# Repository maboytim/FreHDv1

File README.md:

# TRS-HARD disk emulator, aka 'FreHD'

This is a fork of the original FreHD project by Frederic Vecoven.  The original FreHD project can be found on Frederic's site [https://www.vecoven.com/trs80/trs80.html](https://www.vecoven.com/trs80/trs80.html).  The project has since been moved to github at [https://github.com/veco/FreHDv1](https://github.com/veco/FreHDv1) where the latest versions of everything can be found.

The FreHD emulates both the harddisk controller and the disk storage, plus adds many feature which enhance usability.  The FreHD emulates the original TRS-80 harddisk systems such that the original DOS's that supported hardisks should also work with the FreHD using their original harddisk drivers.

The FreHD consists of several components and the scope of the project is really quite amazing.  First there is hardware itself, which uses a PIC microcontroller for a majority of the function, an SD card for the actual storage, a PAL (programmable logic) for miscellaneous logic, and an RTC (realtime clock).  Software (firmware) embedded in the PIC emulates the harddrive and the additional features and provides access to the RTC.  The main purpose of this fork is to provide compatible alternative firmwares, although it goes a bit beyond that.  Although the intent isn't to improve the original project, some improvements and bugfixes have been provided back to the original project.

The equivalent of everything in the original project is included here but might be modified or improved.     My goal is to maintain as much similarity as possible to the original project including the directory structure.  The directory structure is as follows:

+ hw : Hardware files.
  - gal : Equations of the GAL and the compiled jedec file.
  - protel99 : PCB source (schematics and pcb), in Protel99 format for the original PCB design.  Since it is unlikely that anyone is using Protel99 nowadays this is unlikely to change.
  - kicad : PCB source (schematics and pcb), in KiCad format.  This was converted from the original Protel99 design using a conversion script.  It has since been slightly modified and is subject to change.

+ sw : Software files.
  - pic : PIC MPLAB/MPLABX project files, source code, and compiled hex code.
    - trs_hard : 
    - FatFS  : elm FatFS library, ported to PIC18

+ sw/z80
  - fredhd_rom : source code of the boot menu
  - fredhd_rom/rom-patches : patches for all TRS80 models
  - utils : FreHD utilities

To build the PIC software, you will need Microchip C18 compiler (free)
and MPLab (I used version 8.36). You will also need perl, which is
used to compute the CRC16 used by the bootloader. (If you modify the
source, you need to compile twice, the second time to include the
correct CRC in your hex file).

To build the Z80 code, you need zmac. We are using version 1.3, this
assembler is public domain (by Bruce Norskog and others).

To build the rom patches, you need 'asl'. It is available at:
http://john.ccac.rwth-aachen.de:8000/as/

This project started during the long evenings of December 2012, and I
am very proud to release it to the community today, May 12th 2013. 
Many thanks to Andrew Quinn, who beta-tested and motivated me to
finish this project, or at least make it usable :)

One last thing : you may modify, duplicate, enhance or do whatever you
want with the code. All I ask is to keep this README file. You must
make your modifications available (GPL). If you decide to build and
sell (modified) emulators, all I ask is an emulator for my TRS80, so I
can test your changes.

Enjoy !

-Frederic Vecoven (frederic@vecoven.com)

Last update: Thu Jan 23 15:19:26 2014

!!! github !!!
The code is now available on github. I don't have time to
update/polish the code, so contributions are very welcome.

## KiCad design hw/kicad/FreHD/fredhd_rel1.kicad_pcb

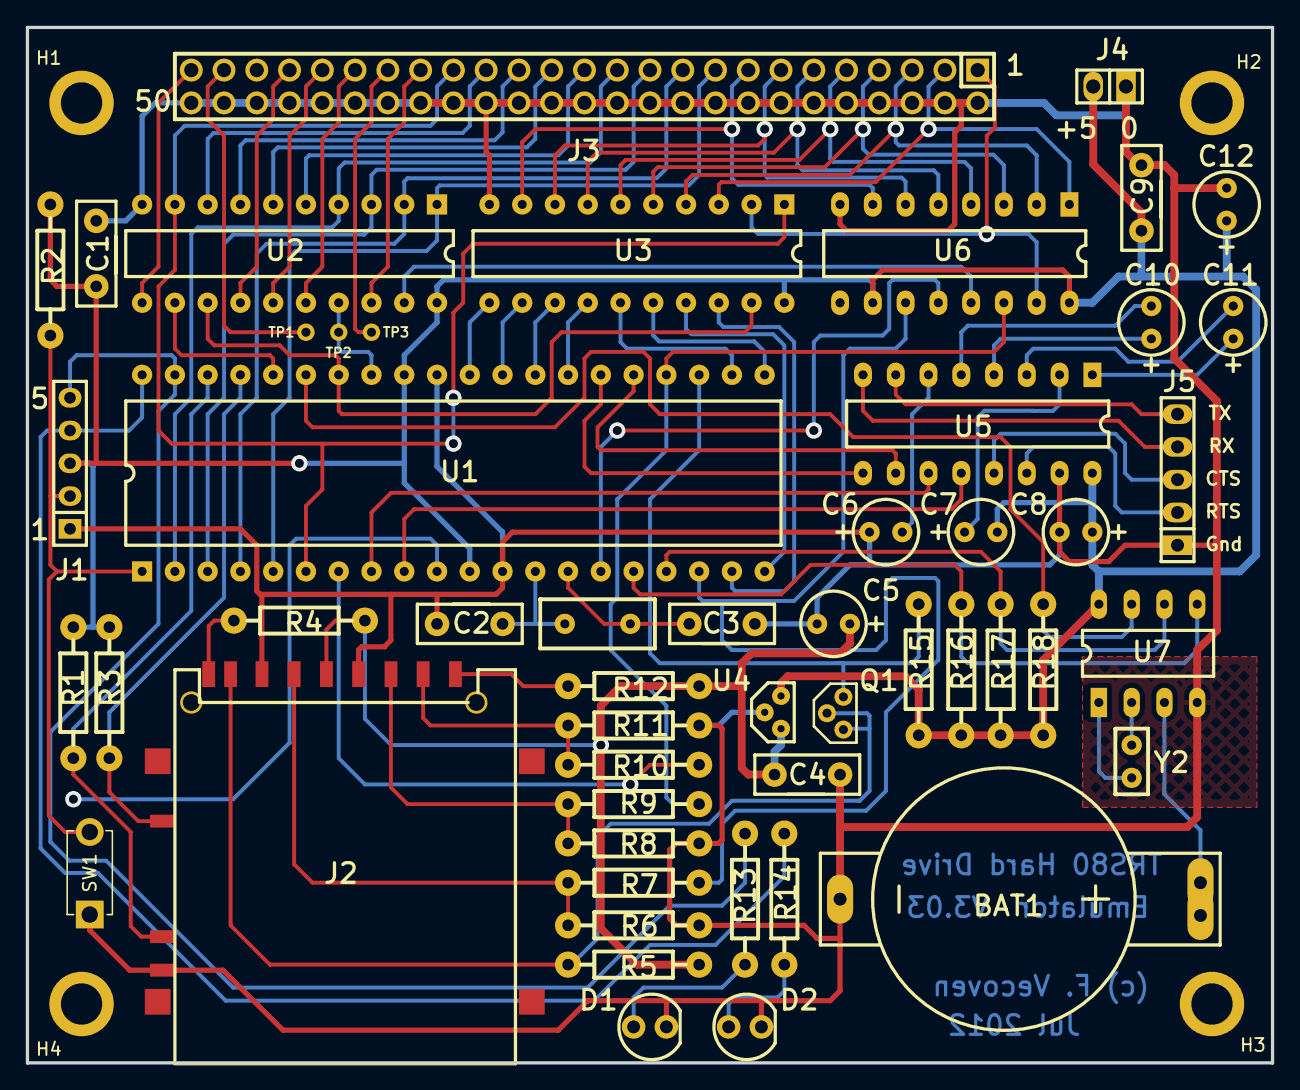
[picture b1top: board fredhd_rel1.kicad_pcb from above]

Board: 2 copper layers, 96.5 x 80.3 mm, 56 parts (0 on the bottom side), 66 nets.

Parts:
BAT1: 3.3V; CR2032
C1, C4, C9: 100n; RAD-0.2
C2, C3: 22p; RAD-0.2
C5, C12: 10u; RB.1
C6, C7, C8, C10, C11: 1uF; RB.1
D1, D2: LED; LEDFRED
H1, H2, H3, H4: MountingHole; MountingHole_3.2mm_M3_DIN965_Pad
J1: CON5; SIP5FS
J2: SDCARD; SDCARD1
J3: CON50; IDC50F
J4: CON2; SIP2
J5: CON5; SIP5F
Q1: BS170; TO92-BS170
R1, R3: 1k; AXI-0.4
R2, R4, R5, R12, R15: 10k; AXI-0.4
R6, R8, R11, R13, R14: 330; AXI-0.4
R7, R9, R10: 220; AXI-0.4
R16, R17, R18: 4k7; AXI-0.4
SW1: SW_Push; PinHeader_1x02_P2.54mm_Vertical
TP1, TP2, TP3: Conn_01x01; PinHeader_1x01_P2.00mm_Vertical
U1: PIC18F4610; DIP40F
U2: GAL16V8; DIP20F
U3: 74HCT245; DIP20F
U4: LP2950-3.3; TO92-LP2950
U5: MAX232; DIP16F
U6: 74HC595; DIP16F
U7: DS1307; DIP8F
Y1: 10MHz; RAD0.2
Y2: 32.768kHz; RAD-0.1

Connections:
3V3: C4.1, C5.1, J2.4 (VDD), R4.2, R5.2, R12.2, U4.3 (Vout)
/A0: J3.17, U1.5 (RA3), U2.1 (IN_0/CLK)
/A1: J3.19, U1.4 (RA2), U2.2 (IN_1)
/A2: J3.21, U1.3 (RA1), U2.3 (IN_2)
/A3: J3.23, U1.2 (RA0), U2.4 (IN_3)
/A4: J3.25, U2.5 (IN_4)
/A5: J3.27, U2.6 (IN_5)
/A6: J3.29, U2.7 (IN_6)
/A7: J3.31, U2.8 (IN_7)
/BUS_INT_N: J3.39, U2.16 (IO_4)
/BUS_WAIT_N: J3.41, U2.15 (IO_3)
/CTS: U1.9 (RE1), U5.12 (R1out)
/D0: J3.1, U3.2 (A1), U6.15 (O0)
/D1: J3.3, U3.3 (A2), U6.1 (O1)
/D2: J3.5, U3.4 (A3), U6.2 (O2)
/D3: J3.7, U3.5 (A4), U6.3 (O3)
/D4: J3.9, U3.6 (A5), U6.4 (O4)
/D5: J3.11, U3.7 (A6), U6.5 (O5)
/D6: J3.13, U3.8 (A7), U6.6 (O6)
/D7: J3.15, U3.9 (A8), U6.7 (O7)
/DD0: U1.19 (RD0), U3.18 (B1)
/DD1: U1.20 (RD1), U3.17 (B2)
/DD2: U1.21 (RD2), U3.16 (B3)
/DD3: U1.22 (RD3), U3.15 (B4)
/DD4: U1.27 (RD4), U3.14 (B5)
/DD5: U1.28 (RD5), U3.13 (B6)
/DD6: U1.29 (RD6), U3.12 (B7)
/DD7: U1.30 (RD7), U3.11 (B8)
/EXTIOSEL_N: J3.43, U2.14 (IO_2)
/IORQ_N: J3.49, U2.11 (~IN_9/OE)
/LED0: J1.4, R14.2, U1.40 (RB7)
/LED1: J1.5, R13.2, U1.39 (RB6)
/M1_N: J3.47, TP1.1
/MCLR: J1.2, R2.2, SW1.2, U1.1 (MCLR)
/OSC1: C2.1, U1.13 (OSC1), Y1.1
/OSC2: C3.1, U1.14 (OSC2), Y1.2
/PIC_SEL_N: U1.34 (RB1), U2.13 (IO_1), U3.19 (~G)
/PIC_WAIT_N: U1.36 (RB3), U2.12 (IO_0)
/RD_N: J3.33, U1.6 (RA4), U2.9 (IN_8), U3.1 (DIR)
/RESET_N: J3.37, TP3.1
/RTC: R18.1, U1.35 (RB2), U7.7 (OUT)
/RTS: U1.8 (RE0), U5.11 (T1in)
/RX: U1.26 (RC7), U5.9 (R2out)
/SCL: R17.1, U1.17 (RC2), U7.6 (SCL)
/SDA: R16.1, U1.16 (RC1), U7.5 (SDA)
/SD_CD: J2.12 (CARD_DETECT), R3.2, U1.37 (RB4)
/SD_CLK_3V3: J2.5 (CLK/SCLK), R6.2, R7.1
/SD_CS_3V3: J2.1 (DAT3/CD/CS), R10.1, R11.2
/SD_CS_5V: R10.2, U1.7 (RA5)
/SD_IN_3V3: J2.2 (CMD/DI), R8.2, R9.1
/SD_WRPROT: J2.11 (WR_PROTECT), R1.2, U1.38 (RB5)
/SPARE1: TP2.1, U1.33 (RB0), U2.17 (IO_5)
/SPI_CLK: R7.2, U1.18 (RC3), U6.11 (SRCLK)
/SPI_SDI: Q1.3 (D), R15.1, U1.23 (RC4)
/SPI_SDI_3V3: J2.7 (DAT0/DO), Q1.1 (G), Q1.2 (S), R5.1
/SPI_SDO: R9.2, U1.24 (RC5), U6.14 (SER)
/STAT_CS: U1.15 (RC0), U6.12 (RCLK)
/STAT_OE_N: U2.19 (IO_7), U6.13 (E)
/TX: U1.25 (RC6), U5.10 (T2in)
/WR_N: J3.35, U2.18 (IO_6)
/oCTS: J5.3, U5.13 (R1in)
/oRTS: J5.2, U5.14 (T1out)
/oRX: J5.4, U5.8 (R2in)
/oTX: J5.5, U5.7 (T2out)
GND: BAT1.1 (+), C1.2, C2.2, C3.2, C4.2, C5.2, C6.1, C8.2, C9.2, C12.2, D1.K (2), D2.K (2), J1.1, J2.3 (VSS1), J2.6 (VSS2), J2.10 (GND_SW), J3.2, J3.4, J3.6, J3.8, J3.10, J3.12, J3.14, J3.16, J3.18, J3.20, J3.22, J3.24, J3.26, J3.28, J3.30, J3.32, J3.34, J3.36, J3.38, J3.40, J3.42, J3.44, J3.46, J3.48, J3.50, J4.1, J5.1, R6.1, R8.1, R11.1, SW1.1, U1.12 (VSS), U1.31 (VSS), U2.10 (GND), U3.10 (GND), U4.2 (GND), U5.15 (Gnd), U6.8 (GND), U7.4 (Gnd)
VCC: C1.1, C7.2, C8.1, C9.1, C12.1, J1.3, J4.2, R1.1, R2.1, R3.1, R15.2, R16.2, R17.2, R18.2, U1.11 (VDD), U1.32 (VDD), U2.20 (VCC), U3.20 (VCC), U4.1 (Vin), U5.16 (Vcc), U6.10 (~SRCLR), U6.16 (VCC), U7.8 (Vdd)

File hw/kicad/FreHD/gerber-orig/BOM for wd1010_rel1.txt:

Bill Of Material For wd1010_rel1.pcb
On 20-Apr-2013 at 10:46:42

 Comment             Pattern     Quantity  Components
------------------------------------------------------------------------------


 100n                RAD-0.2          3    C1, C4, C9

 10MHz               RAD0.2           1    Y1

 10k                 AXI-0.4          5    R2, R4, R5, R12, R15

 10u                 RB.1             2    C5, C12

 1k                  AXI-0.4          2    R1, R3

 1uF                 RB.1             5    C6, C7, C8, C10, C11

 220                 AXI-0.4          3    R7, R9, R10

 22p                 RAD-0.2          2    C2, C3

 3.3V                CR2032           1    BAT1

 32.768kHz           RAD-0.1          1    Y2

 330                 AXI-0.4          5    R6, R8, R11, R13, R14

 4k7                 AXI-0.4          3    R16, R17, R18

 74HC595             DIP16F           1    U6

 74HCT245            DIP20F           1    U3

 BS170               TO92-BS170       1    Q1

 CON2                SIP2             1    J4

 CON5                SIP5F            1    J5

 CON5                SIP5FS           1    J1

 CON50               IDC50F           1    J3

 DS1307              DIP8F            1    U7

 GAL16V8             DIP20F           1    U2

 LED                 LEDFRED          2    D1, D2

 LP2950-3.3          TO92-LP2950      1    U4

 MAX232              DIP16F           1    U5

 PIC18F4620          DIP40F           1    U1

 SDCARD              SDCARD1          1    J2

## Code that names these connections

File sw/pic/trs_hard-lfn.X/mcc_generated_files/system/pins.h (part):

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// get/set RA0 aliases
#define TRS_ADDR3_TRIS                 TRISAbits.TRISA0
#define TRS_ADDR3_LAT                  LATAbits.LATA0
#define TRS_ADDR3_PORT                 PORTAbits.RA0
#define TRS_ADDR3_WPU                  WPUAbits.WPUA0
#define TRS_ADDR3_OD                   ODCONAbits.ODCA0
#define TRS_ADDR3_ANS                  ANSELAbits.ANSELA0
#define TRS_ADDR3_SetHigh()            do { LATAbits.LATA0 = 1; } while(0)
#define TRS_ADDR3_SetLow()             do { LATAbits.LATA0 = 0; } while(0)
#define TRS_ADDR3_Toggle()             do { LATAbits.LATA0 = ~LATAbits.LATA0; } while(0)
#define TRS_ADDR3_GetValue()           PORTAbits.RA0
#define TRS_ADDR3_SetDigitalInput()    do { TRISAbits.TRISA0 = 1; } while(0)
#define TRS_ADDR3_SetDigitalOutput()   do { TRISAbits.TRISA0 = 0; } while(0)
#define TRS_ADDR3_SetPullup()          do { WPUAbits.WPUA0 = 1; } while(0)
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// get/set RA1 aliases
#define TRS_ADDR2_TRIS                 TRISAbits.TRISA1
#define TRS_ADDR2_LAT                  LATAbits.LATA1
#define TRS_ADDR2_PORT                 PORTAbits.RA1
#define TRS_ADDR2_WPU                  WPUAbits.WPUA1
#define TRS_ADDR2_OD                   ODCONAbits.ODCA1
#define TRS_ADDR2_ANS                  ANSELAbits.ANSELA1
#define TRS_ADDR2_SetHigh()            do { LATAbits.LATA1 = 1; } while(0)
#define TRS_ADDR2_SetLow()             do { LATAbits.LATA1 = 0; } while(0)
#define TRS_ADDR2_Toggle()             do { LATAbits.LATA1 = ~LATAbits.LATA1; } while(0)
#define TRS_ADDR2_GetValue()           PORTAbits.RA1
#define TRS_ADDR2_SetDigitalInput()    do { TRISAbits.TRISA1 = 1; } while(0)
#define TRS_ADDR2_SetDigitalOutput()   do { TRISAbits.TRISA1 = 0; } while(0)
#define TRS_ADDR2_SetPullup()          do { WPUAbits.WPUA1 = 1; } while(0)
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// get/set RA2 aliases
#define TRS_ADDR1_TRIS                 TRISAbits.TRISA2
#define TRS_ADDR1_LAT                  LATAbits.LATA2
#define TRS_ADDR1_PORT                 PORTAbits.RA2
#define TRS_ADDR1_WPU                  WPUAbits.WPUA2
#define TRS_ADDR1_OD                   ODCONAbits.ODCA2
#define TRS_ADDR1_ANS                  ANSELAbits.ANSELA2
#define TRS_ADDR1_SetHigh()            do { LATAbits.LATA2 = 1; } while(0)
#define TRS_ADDR1_SetLow()             do { LATAbits.LATA2 = 0; } while(0)
#define TRS_ADDR1_Toggle()             do { LATAbits.LATA2 = ~LATAbits.LATA2; } while(0)
#define TRS_ADDR1_GetValue()           PORTAbits.RA2
#define TRS_ADDR1_SetDigitalInput()    do { TRISAbits.TRISA2 = 1; } while(0)
#define TRS_ADDR1_SetDigitalOutput()   do { TRISAbits.TRISA2 = 0; } while(0)
#define TRS_ADDR1_SetPullup()          do { WPUAbits.WPUA2 = 1; } while(0)
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// get/set RA3 aliases
#define TRS_ADDR0_TRIS                 TRISAbits.TRISA3
#define TRS_ADDR0_LAT                  LATAbits.LATA3
#define TRS_ADDR0_PORT                 PORTAbits.RA3
#define TRS_ADDR0_WPU                  WPUAbits.WPUA3
#define TRS_ADDR0_OD                   ODCONAbits.ODCA3
#define TRS_ADDR0_ANS                  ANSELAbits.ANSELA3
#define TRS_ADDR0_SetHigh()            do { LATAbits.LATA3 = 1; } while(0)
#define TRS_ADDR0_SetLow()             do { LATAbits.LATA3 = 0; } while(0)
#define TRS_ADDR0_Toggle()             do { LATAbits.LATA3 = ~LATAbits.LATA3; } while(0)
#define TRS_ADDR0_GetValue()           PORTAbits.RA3
#define TRS_ADDR0_SetDigitalInput()    do { TRISAbits.TRISA3 = 1; } while(0)
#define TRS_ADDR0_SetDigitalOutput()   do { TRISAbits.TRISA3 = 0; } while(0)
#define TRS_ADDR0_SetPullup()          do { WPUAbits.WPUA3 = 1; } while(0)
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// get/set RA4 aliases
#define TRS_RD_N_TRIS                 TRISAbits.TRISA4
#define TRS_RD_N_LAT                  LATAbits.LATA4
#define TRS_RD_N_PORT                 PORTAbits.RA4
#define TRS_RD_N_WPU                  WPUAbits.WPUA4
#define TRS_RD_N_OD                   ODCONAbits.ODCA4
#define TRS_RD_N_ANS                  ANSELAbits.ANSELA4
#define TRS_RD_N_SetHigh()            do { LATAbits.LATA4 = 1; } while(0)
#define TRS_RD_N_SetLow()             do { LATAbits.LATA4 = 0; } while(0)
#define TRS_RD_N_Toggle()             do { LATAbits.LATA4 = ~LATAbits.LATA4; } while(0)
#define TRS_RD_N_GetValue()           PORTAbits.RA4
#define TRS_RD_N_SetDigitalInput()    do { TRISAbits.TRISA4 = 1; } while(0)
#define TRS_RD_N_SetDigitalOutput()   do { TRISAbits.TRISA4 = 0; } while(0)
#define TRS_RD_N_SetPullup()          do { WPUAbits.WPUA4 = 1; } while(0)
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// get/set RA5 aliases
#define SD_CS_TRIS                 TRISAbits.TRISA5
#define SD_CS_LAT                  LATAbits.LATA5
#define SD_CS_PORT                 PORTAbits.RA5
#define SD_CS_WPU                  WPUAbits.WPUA5
#define SD_CS_OD                   ODCONAbits.ODCA5
#define SD_CS_ANS                  ANSELAbits.ANSELA5
#define SD_CS_SetHigh()            do { LATAbits.LATA5 = 1; } while(0)
#define SD_CS_SetLow()             do { LATAbits.LATA5 = 0; } while(0)
#define SD_CS_Toggle()             do { LATAbits.LATA5 = ~LATAbits.LATA5; } while(0)
#define SD_CS_GetValue()           PORTAbits.RA5
#define SD_CS_SetDigitalInput()    do { TRISAbits.TRISA5 = 1; } while(0)
#define SD_CS_SetDigitalOutput()   do { TRISAbits.TRISA5 = 0; } while(0)
#define SD_CS_SetPullup()          do { WPUAbits.WPUA5 = 1; } while(0)
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// get/set RB0 aliases
#define SPARE1_TRIS                 TRISBbits.TRISB0
#define SPARE1_LAT                  LATBbits.LATB0
#define SPARE1_PORT                 PORTBbits.RB0
#define SPARE1_WPU                  WPUBbits.WPUB0
#define SPARE1_OD                   ODCONBbits.ODCB0
#define SPARE1_ANS                  ANSELBbits.ANSELB0
#define SPARE1_SetHigh()            do { LATBbits.LATB0 = 1; } while(0)
#define SPARE1_SetLow()             do { LATBbits.LATB0 = 0; } while(0)
#define SPARE1_Toggle()             do { LATBbits.LATB0 = ~LATBbits.LATB0; } while(0)
#define SPARE1_GetValue()           PORTBbits.RB0
#define SPARE1_SetDigitalInput()    do { TRISBbits.TRISB0 = 1; } while(0)
#define SPARE1_SetDigitalOutput()   do { TRISBbits.TRISB0 = 0; } while(0)
#define SPARE1_SetPullup()          do { WPUBbits.WPUB0 = 1; } while(0)
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// get/set RB1 aliases
#define GAL_INT_TRIS                 TRISBbits.TRISB1
#define GAL_INT_LAT                  LATBbits.LATB1
#define GAL_INT_PORT                 PORTBbits.RB1
#define GAL_INT_WPU                  WPUBbits.WPUB1
#define GAL_INT_OD                   ODCONBbits.ODCB1
#define GAL_INT_ANS                  ANSELBbits.ANSELB1
#define GAL_INT_SetHigh()            do { LATBbits.LATB1 = 1; } while(0)
#define GAL_INT_SetLow()             do { LATBbits.LATB1 = 0; } while(0)
#define GAL_INT_Toggle()             do { LATBbits.LATB1 = ~LATBbits.LATB1; } while(0)
#define GAL_INT_GetValue()           PORTBbits.RB1
#define GAL_INT_SetDigitalInput()    do { TRISBbits.TRISB1 = 1; } while(0)
#define GAL_INT_SetDigitalOutput()   do { TRISBbits.TRISB1 = 0; } while(0)
#define GAL_INT_SetPullup()          do { WPUBbits.WPUB1 = 1; } while(0)
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// get/set RB2 aliases
#define RTC_INT_TRIS                 TRISBbits.TRISB2
#define RTC_INT_LAT                  LATBbits.LATB2
#define RTC_INT_PORT                 PORTBbits.RB2
#define RTC_INT_WPU                  WPUBbits.WPUB2
#define RTC_INT_OD                   ODCONBbits.ODCB2
#define RTC_INT_ANS                  ANSELBbits.ANSELB2
#define RTC_INT_SetHigh()            do { LATBbits.LATB2 = 1; } while(0)
#define RTC_INT_SetLow()             do { LATBbits.LATB2 = 0; } while(0)
#define RTC_INT_Toggle()             do { LATBbits.LATB2 = ~LATBbits.LATB2; } while(0)
#define RTC_INT_GetValue()           PORTBbits.RB2
#define RTC_INT_SetDigitalInput()    do { TRISBbits.TRISB2 = 1; } while(0)
#define RTC_INT_SetDigitalOutput()   do { TRISBbits.TRISB2 = 0; } while(0)
#define RTC_INT_SetPullup()          do { WPUBbits.WPUB2 = 1; } while(0)
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// get/set RB3 aliases
#define TRS_WAIT_TRIS                 TRISBbits.TRISB3
#define TRS_WAIT_LAT                  LATBbits.LATB3
#define TRS_WAIT_PORT                 PORTBbits.RB3
#define TRS_WAIT_WPU                  WPUBbits.WPUB3
#define TRS_WAIT_OD                   ODCONBbits.ODCB3
#define TRS_WAIT_ANS                  ANSELBbits.ANSELB3
#define TRS_WAIT_SetHigh()            do { LATBbits.LATB3 = 1; } while(0)
#define TRS_WAIT_SetLow()             do { LATBbits.LATB3 = 0; } while(0)
#define TRS_WAIT_Toggle()             do { LATBbits.LATB3 = ~LATBbits.LATB3; } while(0)
#define TRS_WAIT_GetValue()           PORTBbits.RB3
#define TRS_WAIT_SetDigitalInput()    do { TRISBbits.TRISB3 = 1; } while(0)
#define TRS_WAIT_SetDigitalOutput()   do { TRISBbits.TRISB3 = 0; } while(0)
#define TRS_WAIT_SetPullup()          do { WPUBbits.WPUB3 = 1; } while(0)
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// get/set RB4 aliases
#define SD_CD_TRIS                 TRISBbits.TRISB4
#define SD_CD_LAT                  LATBbits.LATB4
#define SD_CD_PORT                 PORTBbits.RB4
#define SD_CD_WPU                  WPUBbits.WPUB4
#define SD_CD_OD                   ODCONBbits.ODCB4
#define SD_CD_ANS                  ANSELBbits.ANSELB4
#define SD_CD_SetHigh()            do { LATBbits.LATB4 = 1; } while(0)
#define SD_CD_SetLow()             do { LATBbits.LATB4 = 0; } while(0)
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
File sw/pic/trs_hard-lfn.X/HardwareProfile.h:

/*
 * Copyright (C) 2013 Frederic Vecoven
 *
 * This file is part of trs_hard
 *
 * trs_hard is free software; you can redistribute it and/or modify
 * it under the terms of the GNU General Public License as published by
 * the Free Software Foundation; either version 3 of the License, or
 * (at your option) any later version.
 *
 * trs_hard is distributed in the hope that it will be useful,
 * but WITHOUT ANY WARRANTY; without even the implied warranty of
 * MERCHANTABILITY or FITNESS FOR A PARTICULAR PURPOSE.  See the
 * GNU General Public License for more details.
 *
 * You should have received a copy of the GNU General Public License
 * along with this program. If not, see <http://www.gnu.org/licenses/>.
 */

#ifndef HARDWARE_PROFILE_H
#define HARDWARE_PROFILE_H
	
#include <xc.h>
	
/** CLOCK FREQUENCY ********************************************/
#define GetSystemClock()		(40000000ul)      // Hz
#define GetInstructionClock()	(GetSystemClock()/4)
#define GetPeripheralClock()	GetInstructionClock()
   
/** I/O pin definitions ****************************************/
#define INPUT_PIN 		1
#define OUTPUT_PIN 		0

/* SD CARD */
#define SD_CS			LATAbits.LATA5		// SD chip select
#define SD_CS_TRIS		TRISAbits.TRISA5	// SD chip select TRIS
#define SPI_SCK_TRIS	TRISCbits.TRISC3	// SPI Clock TRIS
#define SPI_MISO_TRIS	TRISCbits.TRISC4	// SPI Master input/Slave output TRIS
#define SPI_MOSI_TRIS	TRISCbits.TRISC5	// SPI Master output/Slave input TRIS
/*
 * Card write-protect and card detect must be on the same port.
 * If not, adapt diskio.c
 */
#define SD_WP			PORTBbits.RB5		// Card Write Protect
#define SD_WP_TRIS		TRISBbits.TRISB5	// Card Write Protect TRIS
#define SD_WP_PIN		5
#define SD_CD			PORTBbits.RB4		// Card Detect
#define SD_CD_TRIS		TRISBbits.TRISB4	// Card Detect TRIS
#define SD_CD_PIN		4
#define SD_WP_CD_PORT	PORTB

/* STATUS REGISTER */
#define STAT_CS			LATCbits.LATC0		// STATUS LOAD
#define STAT_CS_TRIS	TRISCbits.TRISC0
   
/* TRS80 signals */
#define TRS_ADDR		PORTA				// low nibble is A[3..0] reversed!  RW is bit 4
#define TRS_ADDR_TRIS	TRISA
#define TRS_DATA_IN		PORTD
#define TRS_DATA_OUT	LATD
#define TRS_DATA_TRIS	TRISD
#define TRS_RD_N		PORTAbits.RA4		// 0=read 1=write
#define TRS_RD_N_TRIS	TRISAbits.TRISA4
#define TRS_WAIT		LATBbits.LATB3
#define TRS_WAIT_TRIS	TRISBbits.TRISB3
#define GAL_INT_IE		PIE6bits.INT1IE
#define GAL_INT_IP		IPR6bits.INT1IP
#define GAL_INT_IF		PIR6bits.INT1IF
#define GAL_INT_EDGE	INTCON0bits.INT1EDG
#define GAL_INT_TRIS	TRISBbits.TRISB1
#define GAL_INT			PORTBbits.RB1

/* DS1307 RTC */
#define SDA_LAT			LATCbits.LATC1
#define SDA_PIN			PORTCbits.RC1
#define SDA_TRIS		TRISCbits.TRISC1
#define SCL_LAT			LATCbits.LATC2
#define SCL_PIN			PORTCbits.RC2
#define SCL_TRIS		TRISCbits.TRISC2
#define RTC_INT_IE		PIE10bits.INT2IE
#define RTC_INT_IP		IPR10bits.INT2IP
#define RTC_INT_IF		PIR10bits.INT2IF
#define RTC_INT_EDGE	INTCON0bits.INT2EDG
#define RTC_INT_TRIS	TRISBbits.TRISB2
#define RTC_INT			PORTBbits.RB2

/* Serial Port */
#define TX_TRIS			TRISCbits.TRISC6
#define RX_TRIS			TRISCbits.TRISC7
#define RTS_TRIS		TRISEbits.TRISE0
#define RTS_LAT			LATEbits.LATE0
#define RTS_PIN			PORTEbits.RE0
#define CTS_TRIS		TRISEbits.TRISE1
#define CTS_LAT			LATEbits.LATE1
#define CTS_PIN			PORTEbits.RE1

/* LEDs */
#define GLED			LATBbits.LATB7		// green LED 
#define GLED_TRIS		TRISBbits.TRISB7	// green LED TRIS
#define RLED			LATBbits.LATB6		// red LED
#define RLED_TRIS		TRISBbits.TRISB6	// red LED TRIS

typedef enum {
	LED_OFF,
	LED_ON,
	LED_FAST_BLINK,
	LED_SLOW_BLINK
} led_state_t;
	

/* Spare pins */
#define SPARE1_TRIS		TRISBbits.TRISB0
#define SPARE2_TRIS		TRISEbits.TRISE2

/** USART SETTINGS *********************************************/
#define BAUD_RATE 57600

#endif

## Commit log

2024-08-01 Added trsvid streaming file support to trs_hard firmware for PIC. Changed version to 3.14. Need to update the readme.
2024-08-02 Bugfix to frehd.rom for if the FreHD Firmware or the Loader have a two digit major version. Set the frehd.rom version to 1009h which is one more than was in the original frehd.rom as built.
2024-08-10 Synced with Fred's repo. Added sort feature to frehd.rom. Started adding files for long filenames.
2024-08-10 Added release file FreHD_3.14.hex
2024-08-11 Updated utils for LFN. Added trsvid with LFN support.
2024-08-13 Added MPLABX project for PIC18F47Q83 supporting LFN's. Initial commit still WIP.
2024-08-14 Added MultiDOS OS type to frehd.rom.
2024-08-14 Added patch table entry for MultiDOS.
2024-08-24 Added bootloader for LFN firmware. Synced with changes in main repo.
2024-08-24 Removed crc routines in bootloader.c.
2024-08-25 Replaced mmc crc functions in c with assembly.
2024-08-28 Replaced mcc generated nvm drivers with application code copied from the drivers.
2024-08-28 Changed generate_crc script to generate a c header instead of assembly include.
2024-09-04 Removed mcc generated nvm driver code from bootflasher.
2024-09-06 Minor cleanup.
2024-09-14 Fixed LED blink bug.
2024-09-16 Fix for trsvid bug exposed after LED bugfix.
2024-09-17 Synced with trsvid bugfix in original code. Not actually needed here though.
2024-09-17 Added bootblock protection to bootloader.
2024-09-17 Moved PIC sourcecode pic folder.
2024-09-25 Changed SFN's to use 8.3 name rather than 12 character SFN.
2025-01-12 Corrected references for FAT FS fast seek option from _USE_FASTSEEK to FF_USE_FASTSEEK. Updated FAT FS to R0.15a with 1/9/25 patch. Updated version to 3.55.
2025-02-13 Added dsk.dct
2025-05-17 Added versions of GAL and PIC firmwares.
2025-05-20 Deleted unnecessary build products. Added merged hex files for MplabX projects for convenient programming.
2026-04-18 Added kicad files

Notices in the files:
sw/pic/trs_hard-lfn.X/mcc_generated_files/system/pins.h:
© [2024] Microchip Technology Inc. and its subsidiaries.
